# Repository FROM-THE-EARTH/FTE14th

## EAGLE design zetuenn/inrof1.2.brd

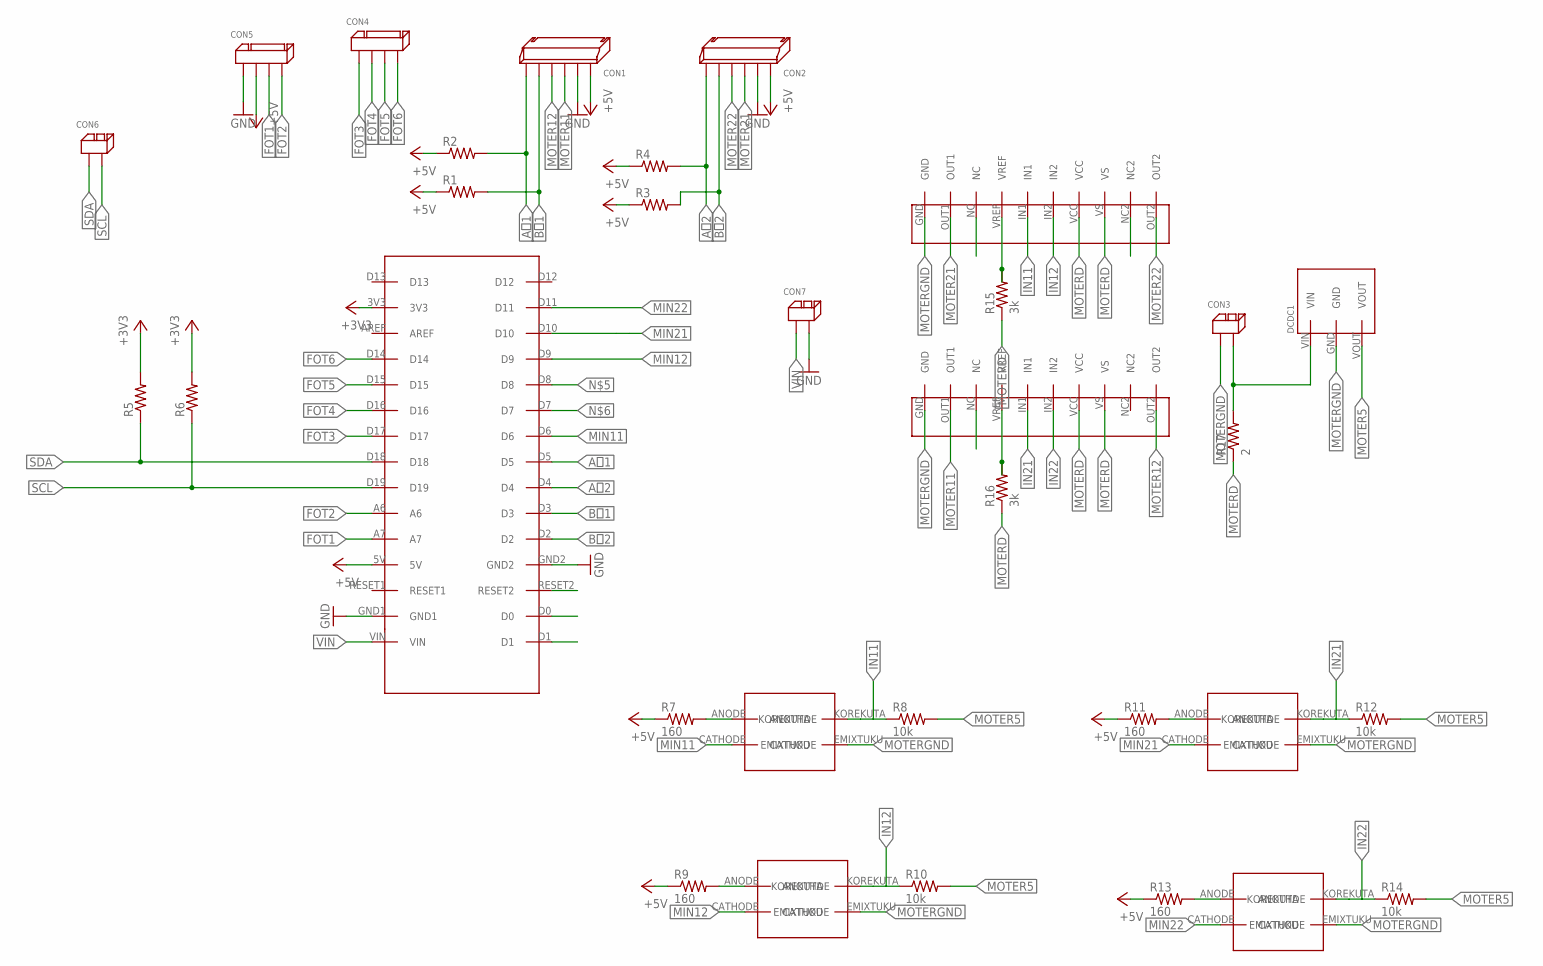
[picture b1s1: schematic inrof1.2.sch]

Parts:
CON1, CON2: 6PIN_SIDE
CON3, CON6, CON7: 2PIN
CON4, CON5: 4PIN
DCDC1: 5V1A_M78AR05-1
R1, R2, R3, R4, R5, R6: R-US_0204/7; 0204/7
R7, R9, R11, R13: 160; 0204/7
R8, R10, R12, R14: 10k; 0204/7
R15, R16: 3k; 0204/7
R17: 2; 0204/7
U$1: ARDUINONANO
U$2, U$3: TA7291P
U$4, U$5, U$6, U$7: TLP561

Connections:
+3V3: R5.2, R6.2, U$1.3V3
+5V: CON1.P$6, CON2.P$6, CON5.P$2, R1.1, R2.1, R3.1, R4.1, R7.1, R9.1, R11.1, R13.1, U$1.5V
A相1: CON1.P$1, R2.2, U$1.D5
A相2: CON2.P$1, R4.2, U$1.D4
B相1: CON1.P$2, R1.2, U$1.D3
B相2: CON2.P$2, R3.2, U$1.D2
FOT1: CON5.P$3, U$1.A7
FOT2: CON5.P$4, U$1.A6
FOT3: CON4.P$1, U$1.D17
FOT4: CON4.P$2, U$1.D16
FOT5: CON4.P$3, U$1.D15
FOT6: CON4.P$4, U$1.D14
GND: CON1.P$5, CON2.P$5, CON5.P$1, CON7.P$2, U$1.GND1, U$1.GND2
IN11: R8.1, U$2.IN1, U$4.KOREKUTA
IN12: R10.1, U$2.IN2, U$5.KOREKUTA
IN21: R12.1, U$3.IN1, U$6.KOREKUTA
IN22: R14.1, U$3.IN2, U$7.KOREKUTA
MIN11: U$1.D6, U$4.CATHODE
MIN12: U$1.D9, U$5.CATHODE
MIN21: U$1.D10, U$6.CATHODE
MIN22: U$1.D11, U$7.CATHODE
MOTER5: DCDC1.VOUT, R8.2, R10.2, R12.2, R14.2
MOTER11: CON1.P$4, U$3.OUT1
MOTER12: CON1.P$3, U$3.OUT2
MOTER21: CON2.P$4, U$2.OUT1
MOTER22: CON2.P$3, U$2.OUT2
MOTERD: CON3.P$2, DCDC1.VIN, R15.1, R16.1, R17.1, R17.2, U$2.VCC, U$2.VS, U$3.VCC, U$3.VS
MOTERGND: CON3.P$1, DCDC1.GND, U$2.GND, U$3.GND, U$4.EMIXTUKU, U$5.EMIXTUKU, U$6.EMIXTUKU, U$7.EMIXTUKU
unnamed: R7.2, U$4.ANODE (ANOTHDE)
unnamed: R15.2, U$2.VREF
unnamed: R16.2, U$3.VREF
unnamed: R9.2, U$5.ANODE (ANOTHDE)
unnamed: R11.2, U$6.ANODE (ANOTHDE)
unnamed: R13.2, U$7.ANODE (ANOTHDE)
SCL: CON6.P$2, R6.1, U$1.D19
SDA: CON6.P$1, R5.1, U$1.D18
VIN: CON7.P$1, U$1.VIN

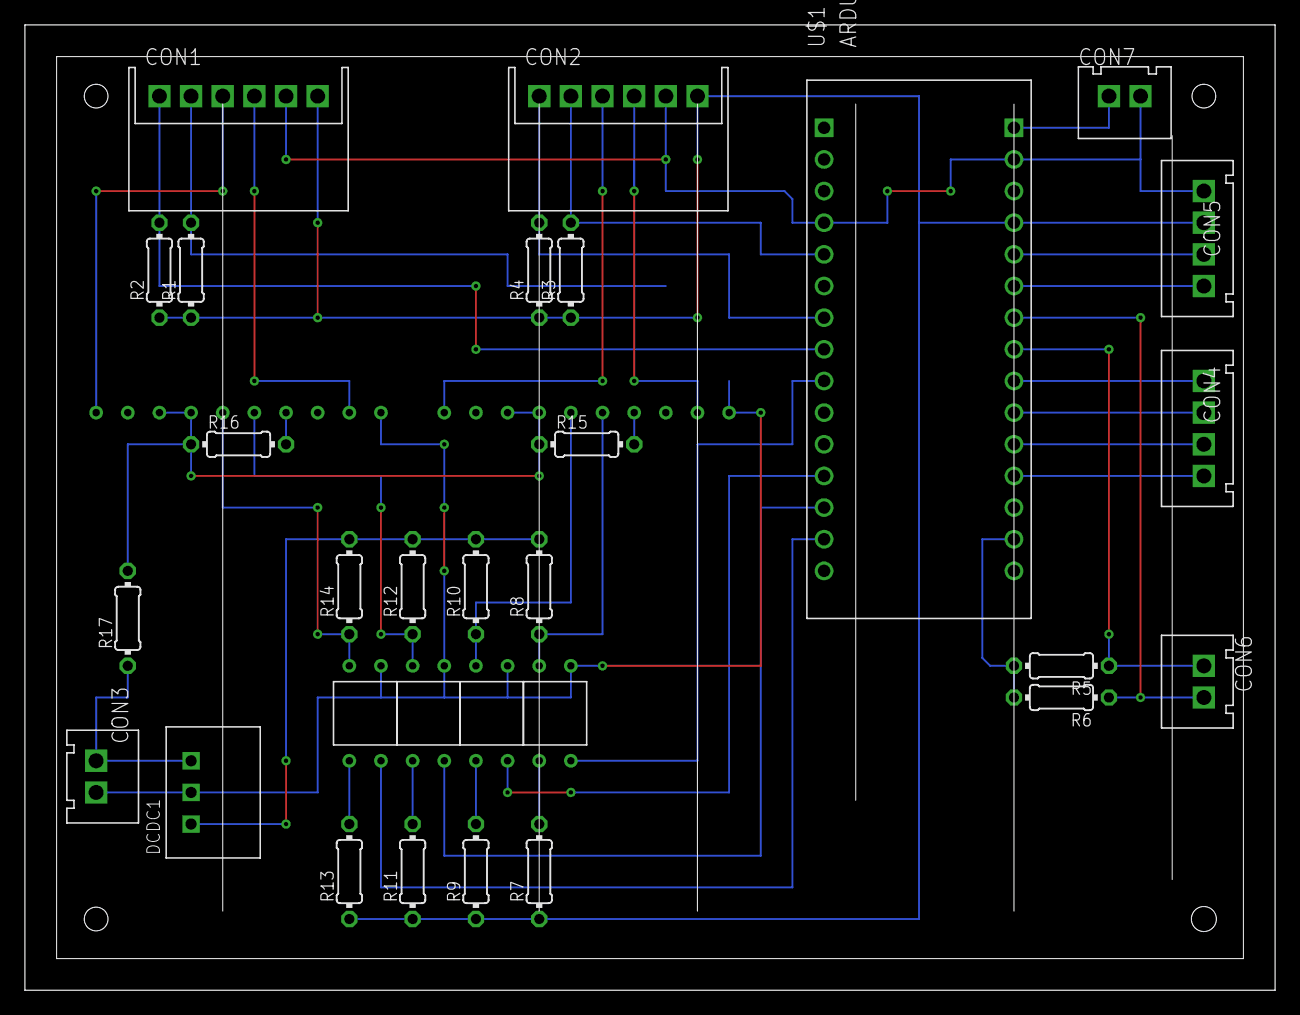
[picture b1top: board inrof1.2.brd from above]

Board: 2 copper layers, 100.3 x 77.5 mm, 32 parts (0 on the bottom side), 37 nets.

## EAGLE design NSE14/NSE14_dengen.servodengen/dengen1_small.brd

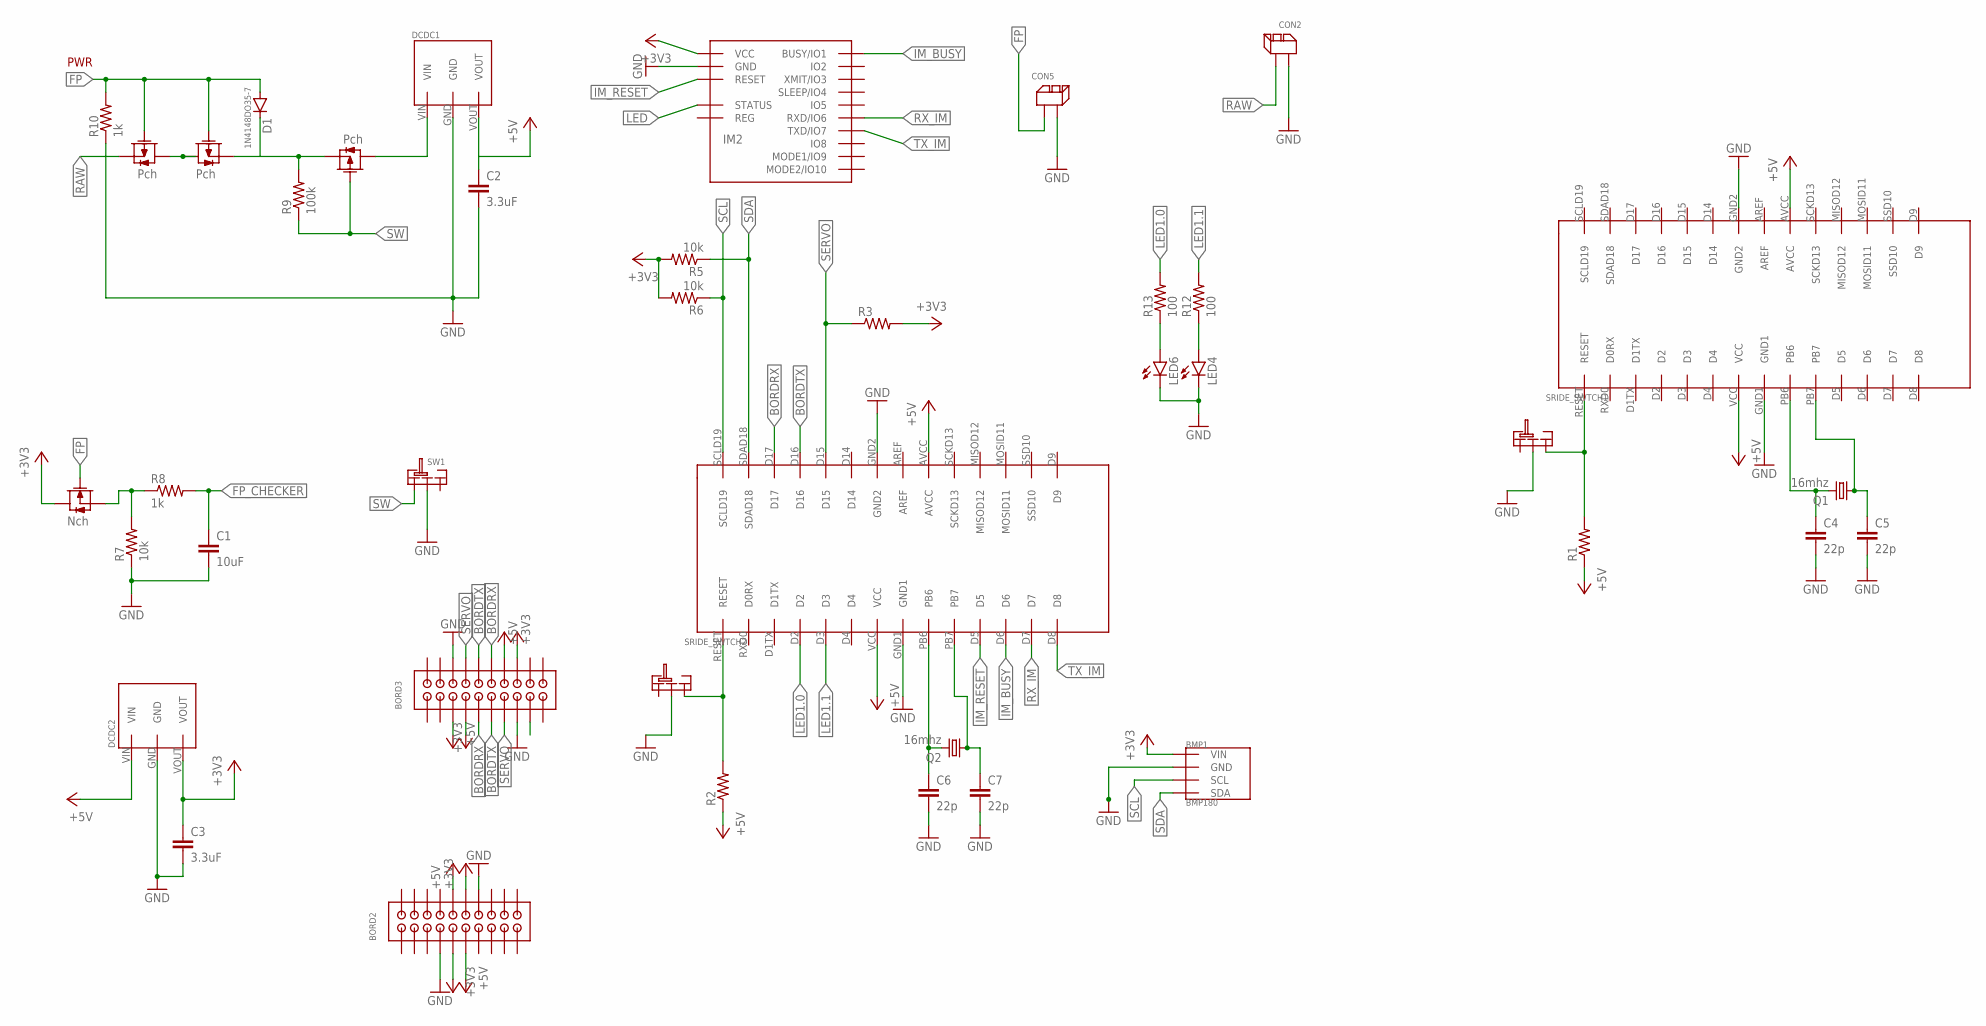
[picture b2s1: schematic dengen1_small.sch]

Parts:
BMP1: BMP180; GY-68
BORD2, BORD3: 2X10
C1: 10uF; C025-024X044
C2, C3: 3.3uF; C025-024X044
C4, C5, C6, C7: 22p; C025-024X044
CON2, CON5: 2PIN
D1: 1N4148DO35-7; DO35-7
DCDC1: 5V1A_M78AR05-1
DCDC2: 3.3V1A_M78AR033-1
IM2: IM920_IM920C
LED4, LED6: LED5MM
Q1, Q2: 16mhz; HC49/S
R1, R2, R3: R-US_0204/7; 0204/7
R5, R6, R7: 10k; 0204/7
R8, R10: 1k; 0204/7
R9: 100k; 0204/7
R12, R13: 100; 0204/7
SRIDE_SWTCH1, SRIDE_SWTCH2: SRIDE_SWITCH
SW1: SRIDE_SWITCH
U$1, U$6: ATMEGA238P; ATMEGA328P
U$2, U$4, U$5: 2SJ681-PCH; 2SJ681
U$3: 2SK4017-NCH; 2SK4017

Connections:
+3V3: BMP1.P1 (VIN), BORD2.P$9, BORD2.P$12, BORD3.P$5, BORD3.P$16, C3.1, DCDC2.VOUT, IM2.$P17 (VCC), R3.2, R5.2, R6.2, U$3.DRAIN
+5V: BORD2.P$10, BORD2.P$11, BORD3.P$7, BORD3.P$14, C2.1, DCDC1.VOUT, DCDC2.VIN, R1.1, R2.1, U$1.AVCC, U$1.VCC, U$6.AVCC, U$6.VCC
+5V1: DCDC1.VIN, U$5.DRAIN
BORDRX: BORD3.P$9, BORD3.P$12, U$6.D17
BORDTX: BORD3.P$10, BORD3.P$11, U$6.D16
FP: CON5.P$1, D1.A, R10.2, U$2.GATE, U$3.GATE, U$4.GATE
FP_CHECKER: C1.1, R8.2
GND: BMP1.P2 (GND), BORD2.P$7, BORD2.P$14, BORD3.P$6, BORD3.P$15, C1.2, C2.2, C3.2, C4.2, C5.2, C6.2, C7.2, CON2.P$1, CON5.P$2, DCDC1.GND, DCDC2.GND, IM2.$P18 (GND), LED4.K (C), LED6.K (C), R7.1, R10.1, SRIDE_SWTCH1.LR, SRIDE_SWTCH2.LR, SW1.LR, U$1.GND1, U$1.GND2, U$6.GND1, U$6.GND2
IM_BUSY: IM2.$P1 (BUSY/IO1), U$6.D6
IM_RESET: IM2.$P19 (RESET), U$6.D5
LED: IM2.$P15 (STATUS)
LED1.0: R13.2, U$6.D2
LED1.1: R12.2, U$6.D3
unnamed: U$2.DRAIN, U$4.DRAIN
unnamed: C6.1, Q2.2, U$6.PB6
unnamed: D1.C, R9.2, U$4.SOURCE, U$5.SOURCE
unnamed: C7.1, Q2.1, U$6.PB7
unnamed: C5.1, Q1.1, U$1.PB7
unnamed: R1.2, SRIDE_SWTCH1.R, U$1.RESET
unnamed: C4.1, Q1.2, U$1.PB6
unnamed: R2.2, SRIDE_SWTCH2.R, U$6.RESET
unnamed: LED6.A, R13.1
unnamed: LED4.A, R12.1
unnamed: R7.2, R8.1, U$3.SOURCE
RAW: CON2.P$2, U$2.SOURCE
RX_IM: IM2.$P6 (RXD/IO6), U$6.D7
SCL: BMP1.P3 (SCL), R6.1, U$6.SCLD19
SDA: BMP1.P4 (SDA), R5.1, U$6.SDAD18
SERVO: BORD3.P$8, BORD3.P$13, R3.1, U$6.D15
SW: R9.1, SW1.L, U$5.GATE
TX_IM: IM2.$P7 (TXD/IO7), U$6.D8

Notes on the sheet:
PWR

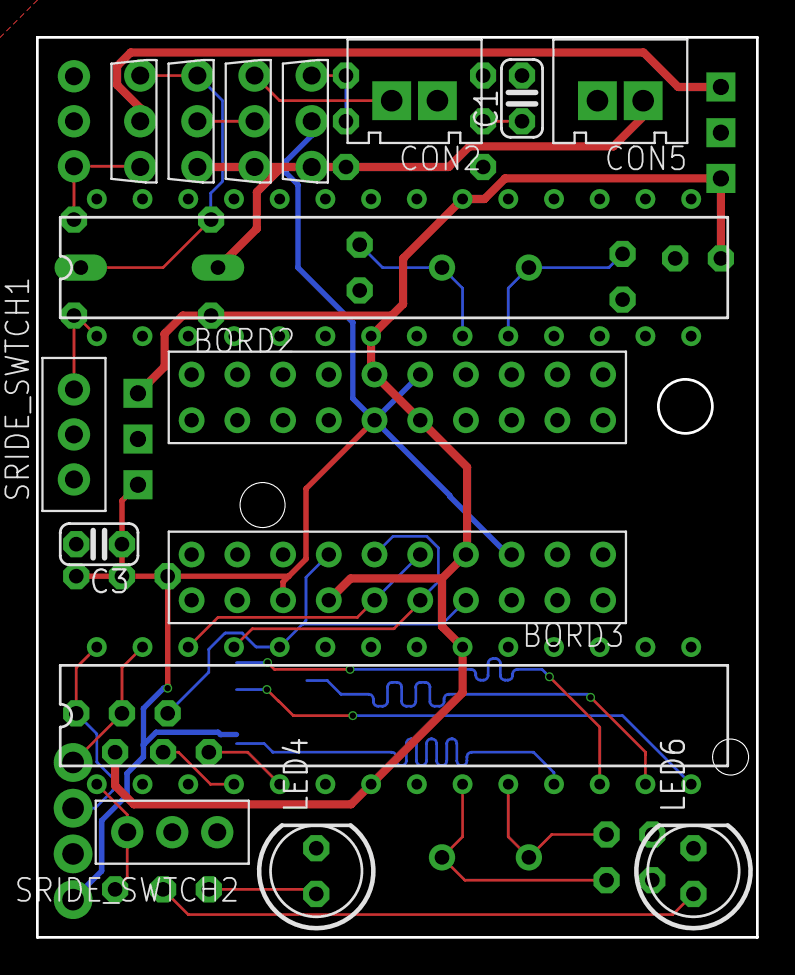
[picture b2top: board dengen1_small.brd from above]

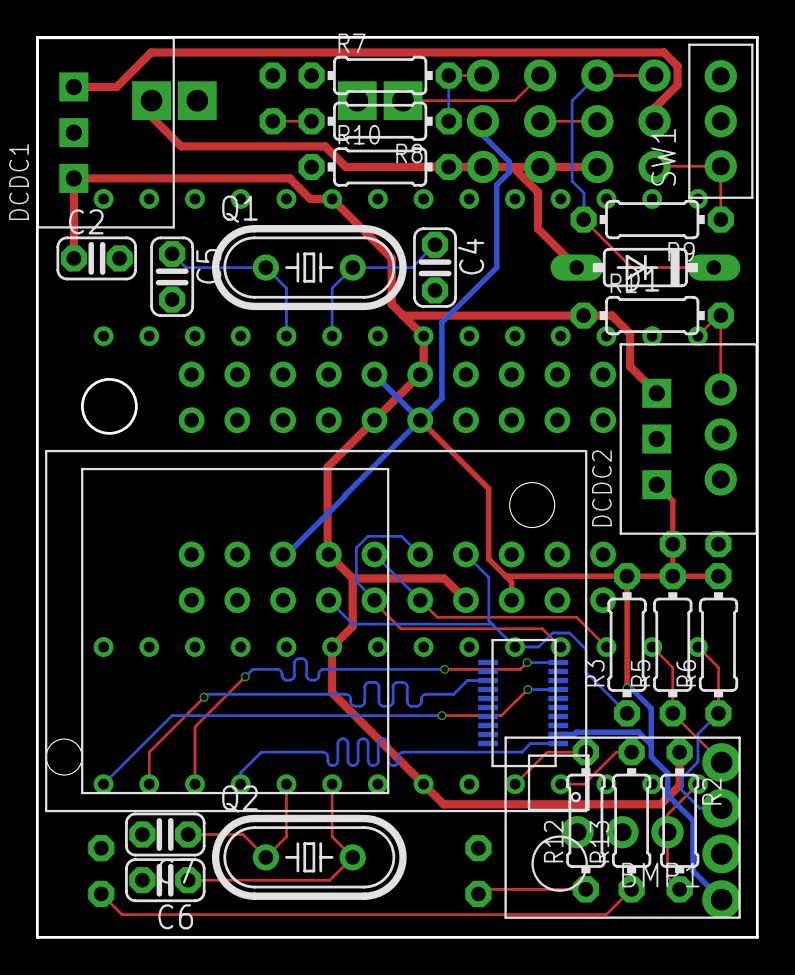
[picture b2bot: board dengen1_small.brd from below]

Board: 2 copper layers, 40.0 x 50.0 mm, 40 parts (24 on the bottom side), 30 nets.

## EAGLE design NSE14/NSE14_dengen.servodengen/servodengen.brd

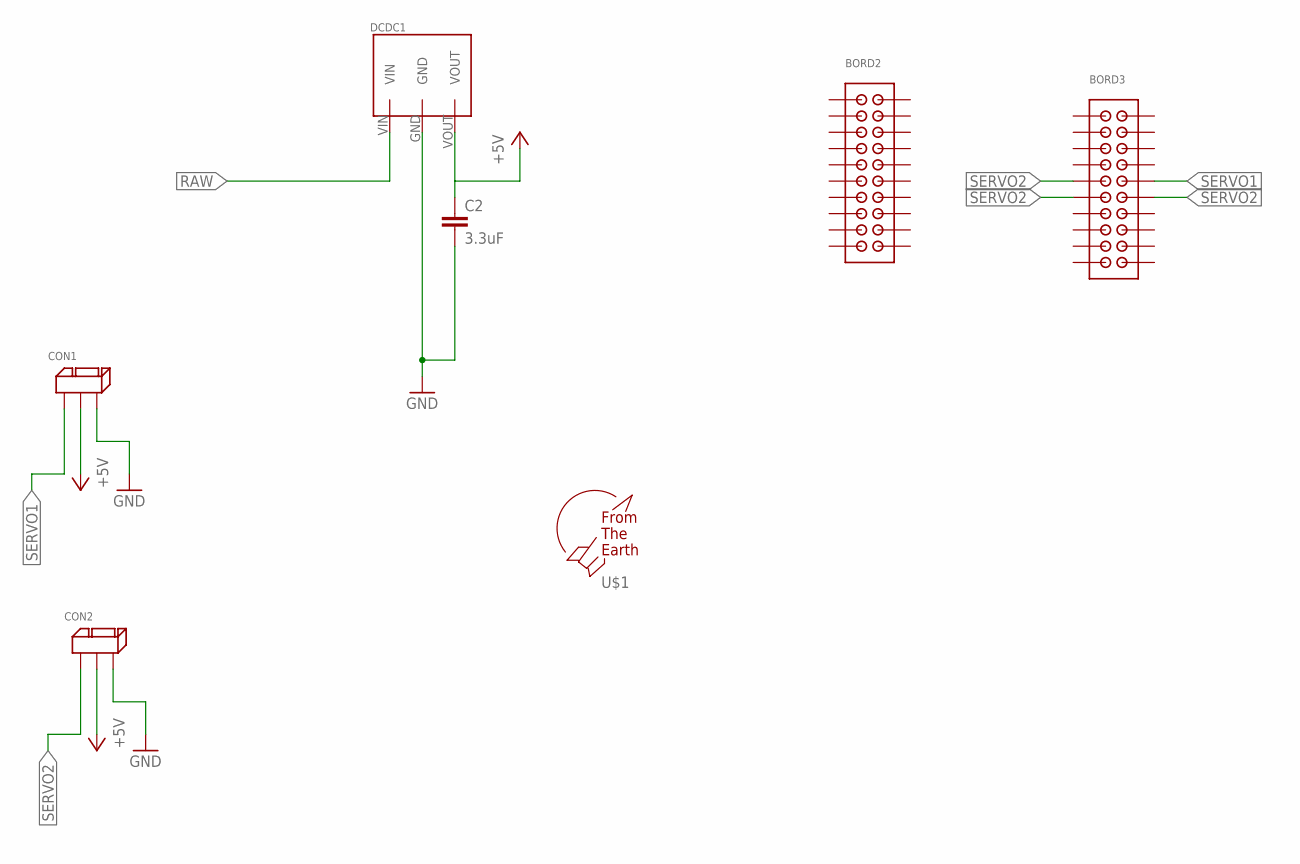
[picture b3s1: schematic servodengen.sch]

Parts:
BORD2, BORD3: 2X10
C2: 3.3uF; C025-024X044
CON1, CON2: 3PIN
DCDC1: 5V1A_M78AR05-1
U$1: F.T.E.LOGO; LOGO

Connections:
+5V: C2.1, CON1.P$2, CON2.P$2, DCDC1.VOUT
GND: C2.2, CON1.P$3, CON2.P$3, DCDC1.GND
RAW: DCDC1.VIN
SERVO1: BORD3.P$10, CON1.P$1
SERVO2: BORD3.P$9, BORD3.P$11, BORD3.P$12, CON2.P$1

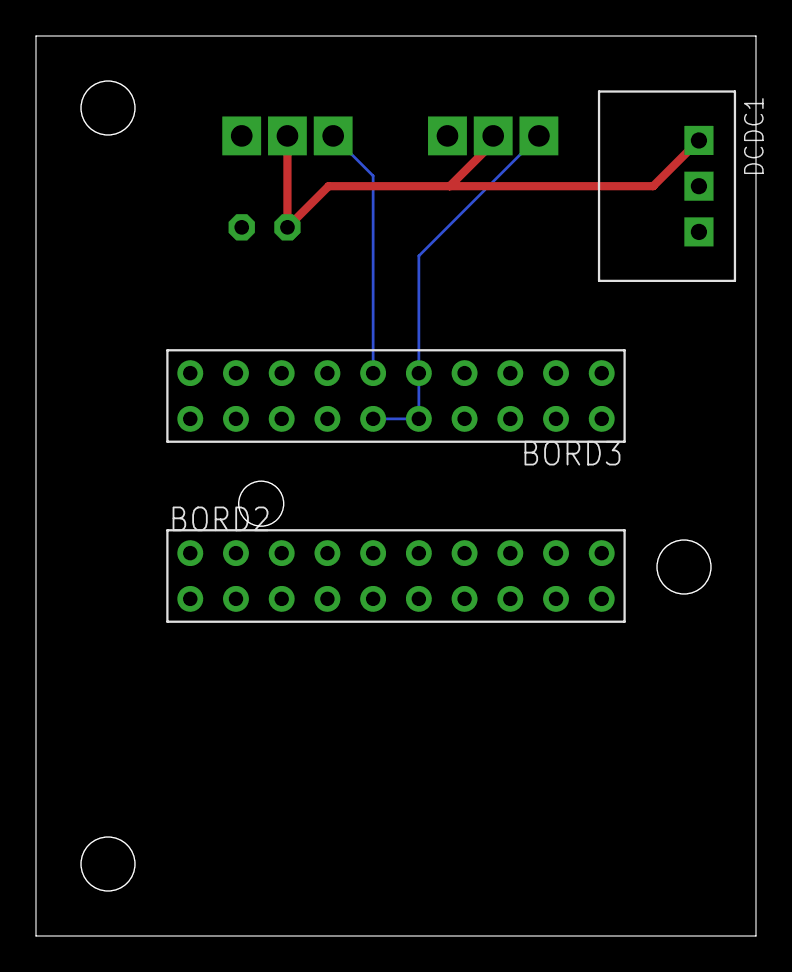
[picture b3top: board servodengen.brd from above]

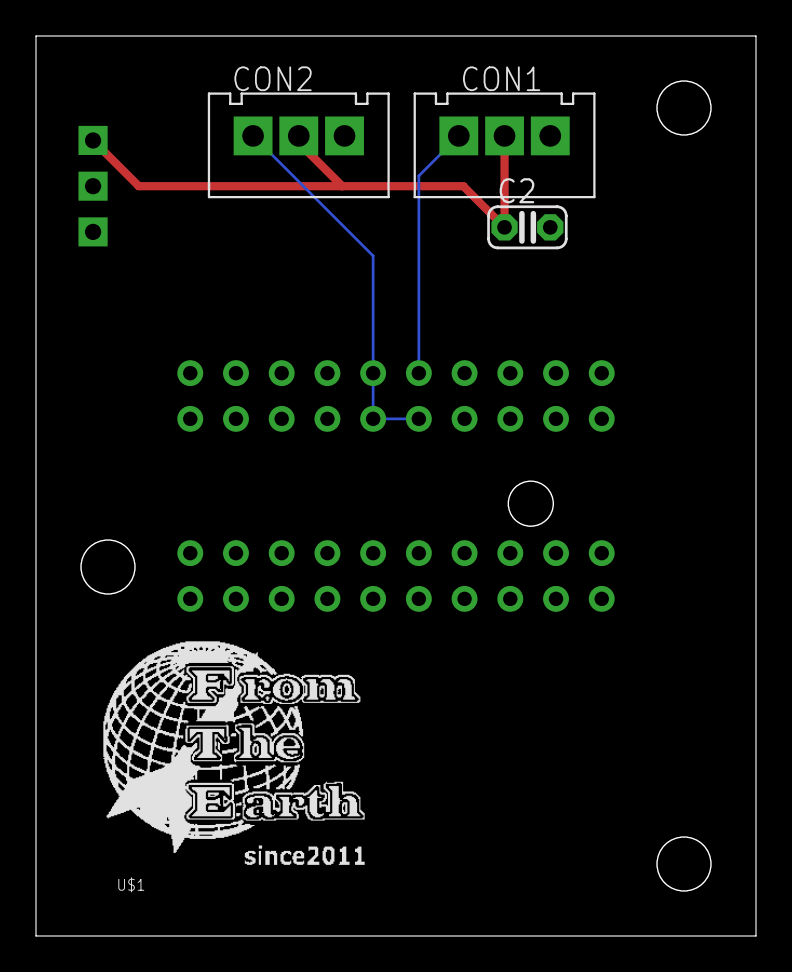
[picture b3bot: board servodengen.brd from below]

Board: 2 copper layers, 40.0 x 50.0 mm, 7 parts (4 on the bottom side), 4 nets.

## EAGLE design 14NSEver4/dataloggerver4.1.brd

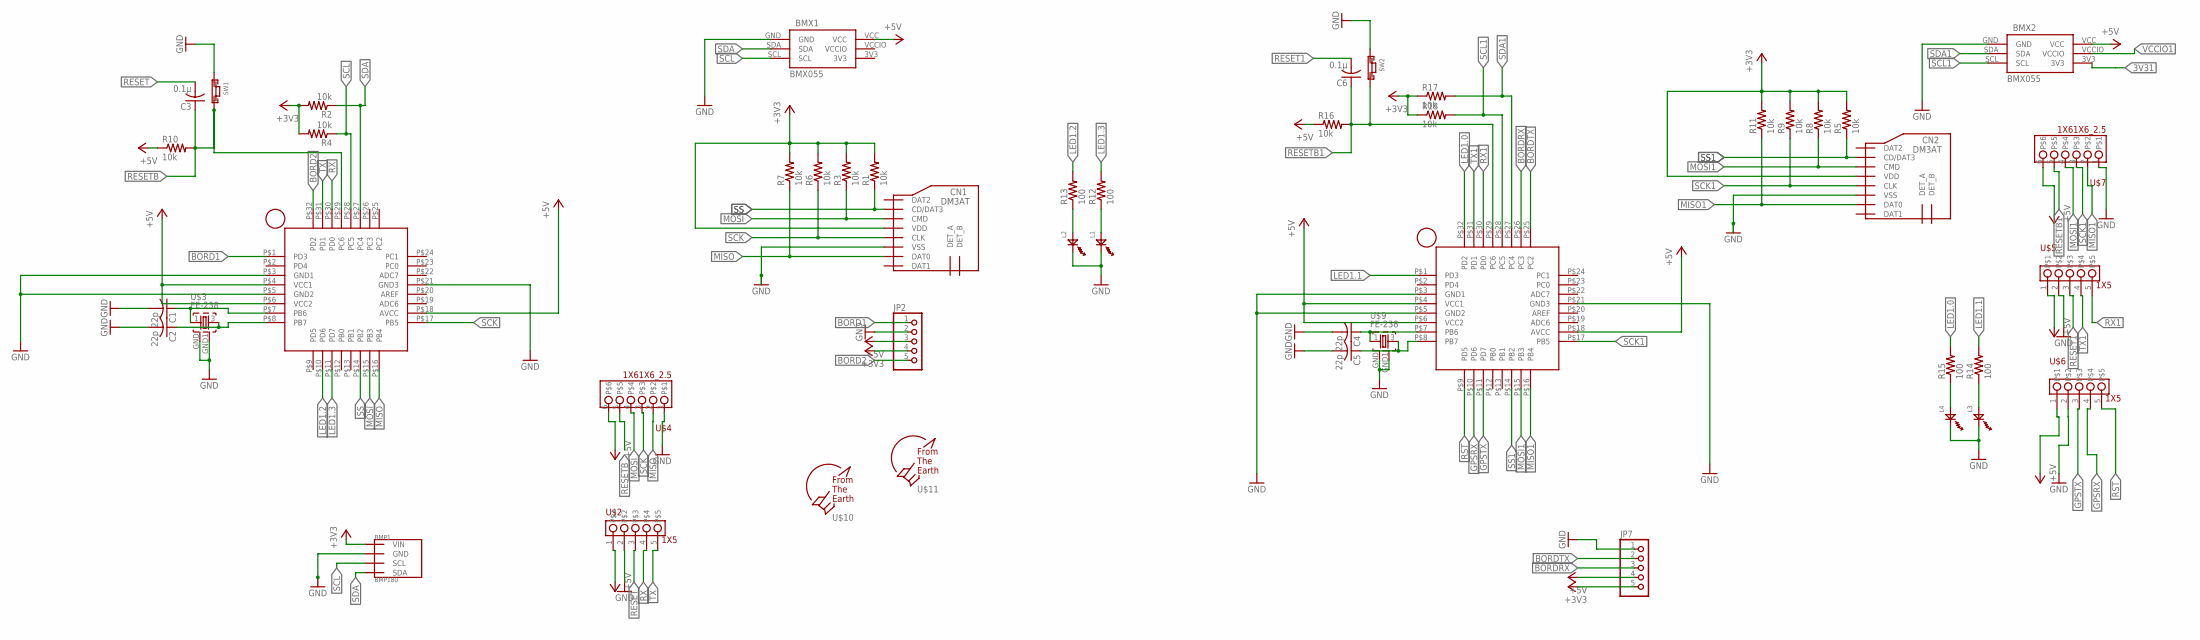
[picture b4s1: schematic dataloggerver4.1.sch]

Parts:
BMP1: BMP180; GY-68
BMX1, BMX2: BMX055
C1, C2, C4, C5: 22p; C1608
C3, C6: 0.1μ; C1608
CN1, CN2: DM3AT
JP2, JP7: PINHD-1X5; 1X05
L1, L2, L3, L4: OSXX1608C1A
R1, R2, R3, R4, R5, R6, R7, R8, R9, R10, R11, R16, R17, R18: 10k; R0603
R12, R13, R14, R15: 100; R0603
SW1, SW2: TVAF06-A020B-R
U$1, U$8: ATMEGA328P-AUATMEGA328P-AU; ATMEGA328P-AU
U$2, U$5, U$6: 1X5; HDRVR5W64P254_1X5_1310X250X865B
U$3, U$9: FE-238; OSCCC300X230X120N
U$4, U$7: 1X61X6_2.5; HDRVR6W64P254_1X6_1564X250X865B
U$10, U$11: F.T.E.LOGO; LOGO

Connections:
3V3: BMX1.3V3
3V31: BMX2.3V3
+3V3: BMP1.P1 (VIN), CN1.VDD, CN2.VDD, JP2.4, JP7.5, R1.2, R2.2, R3.2, R4.2, R5.2, R6.2, R7.2, R8.2, R9.2, R11.2, R17.1, R18.1
+5V: BMX1.VCC, BMX2.VCC, JP2.3, JP7.4, R10.1, R16.1, U$1.P$4 (VCC1), U$1.P$6 (VCC2), U$1.P$18 (AVCC), U$2.1, U$4.6, U$5.1, U$6.1, U$7.6, U$8.P$4 (VCC1), U$8.P$6 (VCC2), U$8.P$18 (AVCC)
BORD1: JP2.1, U$8.P$1 (PD3)
BORD2: JP2.5, U$8.P$32 (PD2)
BORDRX: JP7.3, U$1.P$26 (PC3)
BORDTX: JP7.2, U$1.P$25 (PC2)
GND: BMP1.P2 (GND), BMX1.GND, BMX2.GND, C1.2, C2.2, C4.2, C5.2, CN1.VSS, CN2.VSS, JP2.2, JP7.1, L1.CT, L2.CT, L3.CT, L4.CT, SW1.P$1, SW2.P$1, U$1.P$3 (GND1), U$1.P$5 (GND2), U$1.P$21 (GND3), U$2.2, U$3.GND, U$3.GND1, U$4.1, U$5.2, U$6.2, U$7.1, U$8.P$3 (GND1), U$8.P$5 (GND2), U$8.P$21 (GND3), U$9.GND, U$9.GND1
GPSRX: U$1.P$10 (PD6), U$6.4
GPSTX: U$1.P$11 (PD7), U$6.3
LED1.0: R15.2, U$1.P$32 (PD2)
LED1.1: R14.2, U$1.P$1 (PD3)
LED1.2: R13.2, U$8.P$10 (PD6)
LED1.3: R12.2, U$8.P$11 (PD7)
MISO: CN1.DAT0, R7.1, U$4.2, U$8.P$16 (PB4)
MISO1: CN2.DAT0, R11.1, U$1.P$16 (PB4), U$7.2
MOSI: CN1.CMD, R3.1, U$4.4, U$8.P$15 (PB3)
MOSI1: CN2.CMD, R8.1, U$1.P$15 (PB3), U$7.4
unnamed: L2.AN, R13.1
unnamed: L4.AN, R15.1
unnamed: C4.1, U$1.P$7 (PB6), U$9.1
unnamed: L1.AN, R12.1
unnamed: L3.AN, R14.1
unnamed: C5.1, U$1.P$8 (PB7), U$9.3
unnamed: C1.1, U$3.1, U$8.P$7 (PB6)
unnamed: C2.1, U$3.3, U$8.P$8 (PB7)
RESET: C3.2, U$2.3
RESET1: C6.2, U$5.3
RESETB: C3.1, R10.2, SW1.P$2, U$4.5, U$8.P$29 (PC6)
RESETB1: C6.1, R16.2, SW2.P$2, U$1.P$29 (PC6), U$7.5
RST: U$1.P$9 (PD5), U$6.5
RX: U$2.4, U$8.P$30 (PD0)
RX1: U$1.P$30 (PD0), U$5.5
SCK: CN1.CLK, R6.1, U$4.3, U$8.P$17 (PB5)
SCK1: CN2.CLK, R9.1, U$1.P$17 (PB5), U$7.3
SCL: BMP1.P3 (SCL), BMX1.SCL, R4.1, U$8.P$28 (PC5)
SCL1: BMX2.SCL, R18.2, U$1.P$28 (PC5)
SDA: BMP1.P4 (SDA), BMX1.SDA, R2.1, U$8.P$27 (PC4)
SDA1: BMX2.SDA, R17.2, U$1.P$27 (PC4)
SS: CN1.CD/DAT3, R1.1, U$8.P$14 (PB2)
SS1: CN2.CD/DAT3, R5.1, U$1.P$14 (PB2)
TX: U$2.5, U$8.P$31 (PD1)
TX1: U$1.P$31 (PD1), U$5.4
VCCIO: BMX1.VCCIO
VCCIO1: BMX2.VCCIO

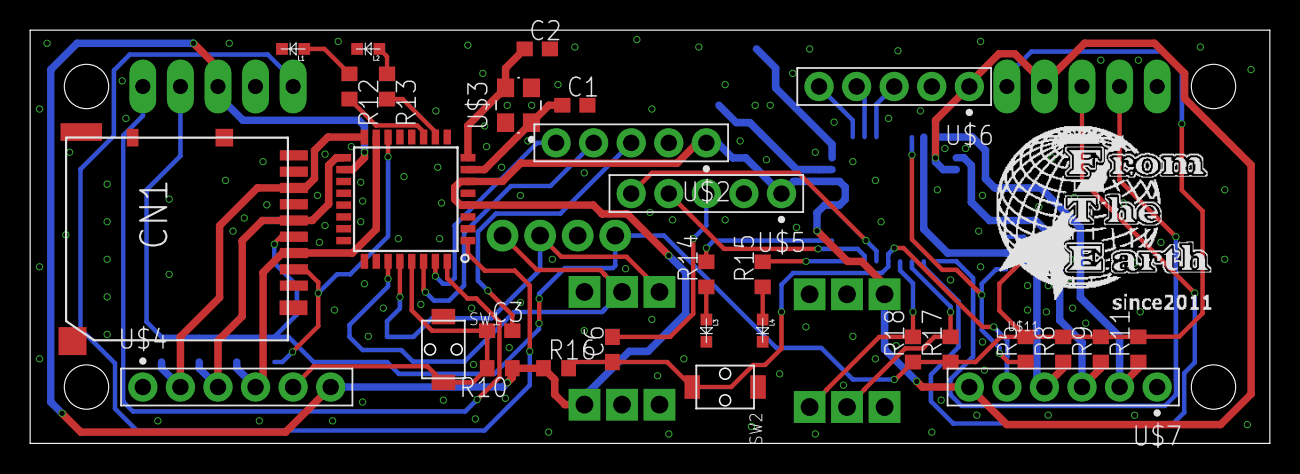
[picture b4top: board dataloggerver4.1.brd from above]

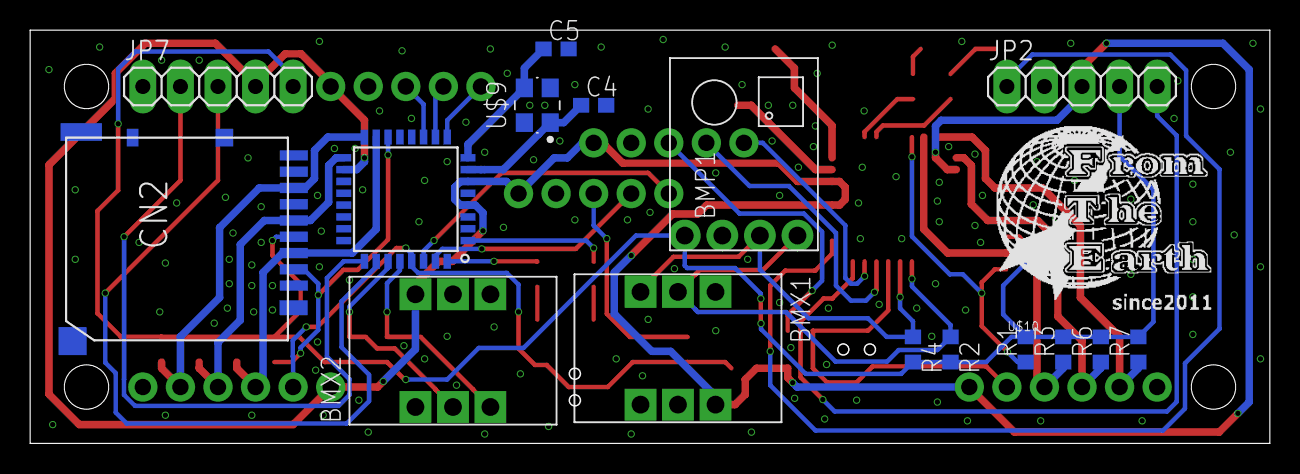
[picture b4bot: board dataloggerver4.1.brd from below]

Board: 2 copper layers, 83.8 x 27.9 mm, 48 parts (17 on the bottom side), 42 nets.

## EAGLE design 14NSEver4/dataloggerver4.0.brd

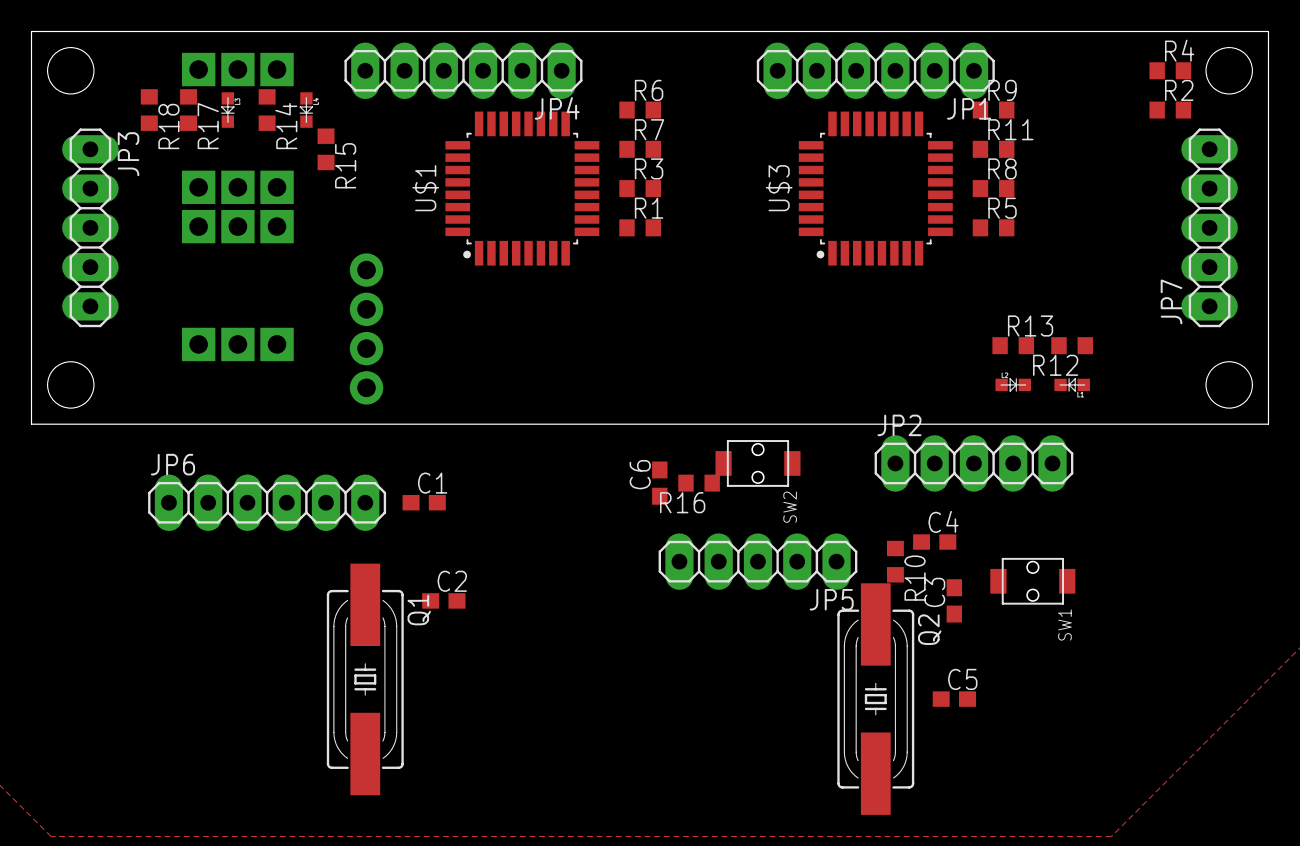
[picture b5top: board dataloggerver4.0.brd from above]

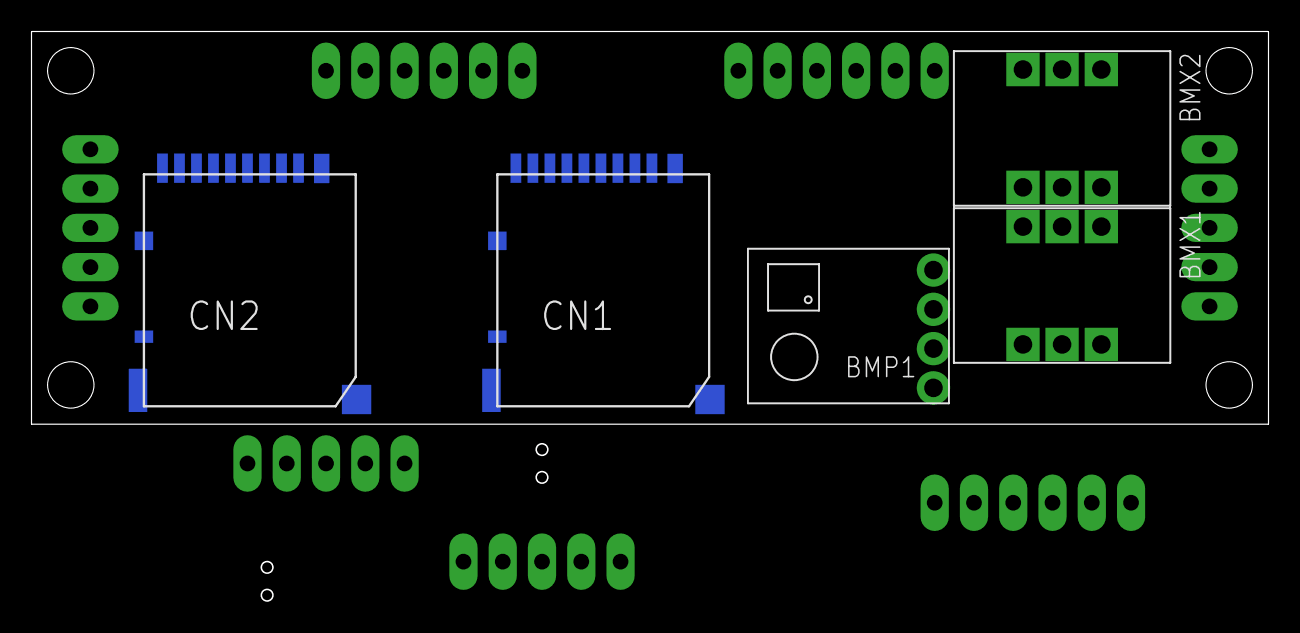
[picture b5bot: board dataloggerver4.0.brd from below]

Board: 2 copper layers, 80.0 x 36.8 mm, 46 parts (5 on the bottom side), 44 nets, no tracks yet.

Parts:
BMP1: BMP180; GY-68
BMX1, BMX2: BMX055
C1, C2, C4, C5: 22p; C1608
C3, C6: 0.1μ; C1608
CN1, CN2: DM3AT
JP1, JP4, JP6: 1X06
JP2, JP3, JP5, JP7: 1X05
L1, L2, L3, L4: OSXX1608C1A
Q1, Q2: 16mhz; HC49UP
R1, R2, R3, R4, R5, R6, R7, R8, R9, R10, R11, R16, R17, R18: 10k; R0603
R12, R13, R14, R15: 100; R0603
SW1, SW2: TVAF06-A020B-R
U$1, U$3: ATMEGA328P-AU; QFP80P900X900X120-32N

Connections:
3V3: BMX1.3V3, BMX2.3V3
+3V3: BMP1.P1, CN1.VDD, CN2.VDD, JP3.4, JP7.5, R1.2, R2.2, R3.2, R4.2, R5.2, R6.2, R7.2, R8.2, R9.2, R11.2, R17.1, R18.1
+5V: BMX1.VCC, BMX2.VCC, JP1.1, JP2.1, JP3.3, JP4.1, JP5.1, JP6.1, JP7.4, R10.1, R16.1, U$1.AVCC, U$1.VCC, U$1.VCC2, U$3.AVCC, U$3.VCC, U$3.VCC2
BORD1: JP3.1, U$1.PD3
BORD2: JP3.5, U$1.PD2
BORDRX: JP7.3, U$3.PC3
BORDTX: JP7.2, U$3.PC2
GND: BMP1.P2, BMX1.GND, BMX2.GND, C1.2, C2.2, C4.2, C5.2, CN1.VSS, CN2.VSS, JP1.2, JP2.2, JP3.2, JP4.2, JP5.2, JP6.2, JP7.1, L1.CT, L2.CT, L3.CT, L4.CT, SW1.P$1, SW2.P$1, U$1.GND, U$1.GND2, U$1.GND3, U$3.GND, U$3.GND2, U$3.GND3
GPSRX: JP6.4, U$3.PD6
GPSTX: JP6.3, U$3.PD7
LED1.0: R15.2, U$3.PD2
LED1.1: R14.2, U$3.PD3
LED1.2: R13.2, U$1.PD6
LED1.3: R12.2, U$1.PD7
MISO: CN1.DAT0, JP1.4, R7.1, U$1.PB4MISO
MISO1: CN2.DAT0, JP4.4, R11.1, U$3.PB4MISO
MOSI: CN1.CMD, JP1.5, R3.1, U$1.PB3MOSI
MOSI1: CN2.CMD, JP4.5, R8.1, U$3.PB3MOSI
unnamed: L2.AN, R13.1
unnamed: L4.AN, R15.1
unnamed: C4.1, Q2.1, U$3.PB6
unnamed: L1.AN, R12.1
unnamed: L3.AN, R14.1
unnamed: C1.1, Q1.1, U$1.PB6
unnamed: C2.1, Q1.2, U$1.PB7
unnamed: C5.1, Q2.2, U$3.PB7
RESET: C3.2, JP2.3
RESET1: C6.2, JP5.3
RESETB: C3.1, JP1.6, R10.2, SW1.P$2, U$1.PC6RESET
RESETB1: C6.1, JP4.6, R16.2, SW2.P$2, U$3.PC6RESET
RST: JP6.5, U$3.PD5
RX: JP2.4, U$1.PD0RX
RX1: JP5.4, U$3.PD0RX
SCK: CN1.CLK, JP1.3, R6.1, U$1.PB5
SCK1: CN2.CLK, JP4.3, R9.1, U$3.PB5
SCL: BMP1.P3, BMX1.SCL, R4.1, U$1.PC5SCL
SCL1: BMX2.SCL, R18.2, U$3.PC5SCL
SDA: BMP1.P4, BMX1.SDA, R2.1, U$1.PC4SDA
SDA1: BMX2.SDA, R17.2, U$3.PC4SDA
SS: CN1.CD/DAT3, R1.1, U$1.PB2SS
SS1: CN2.CD/DAT3, R5.1, U$3.PB2SS
TX: JP2.5, U$1.PD1TX
TX1: JP5.5, U$3.PD1TX
VCCIO: BMX1.VCCIO, BMX2.VCCIO

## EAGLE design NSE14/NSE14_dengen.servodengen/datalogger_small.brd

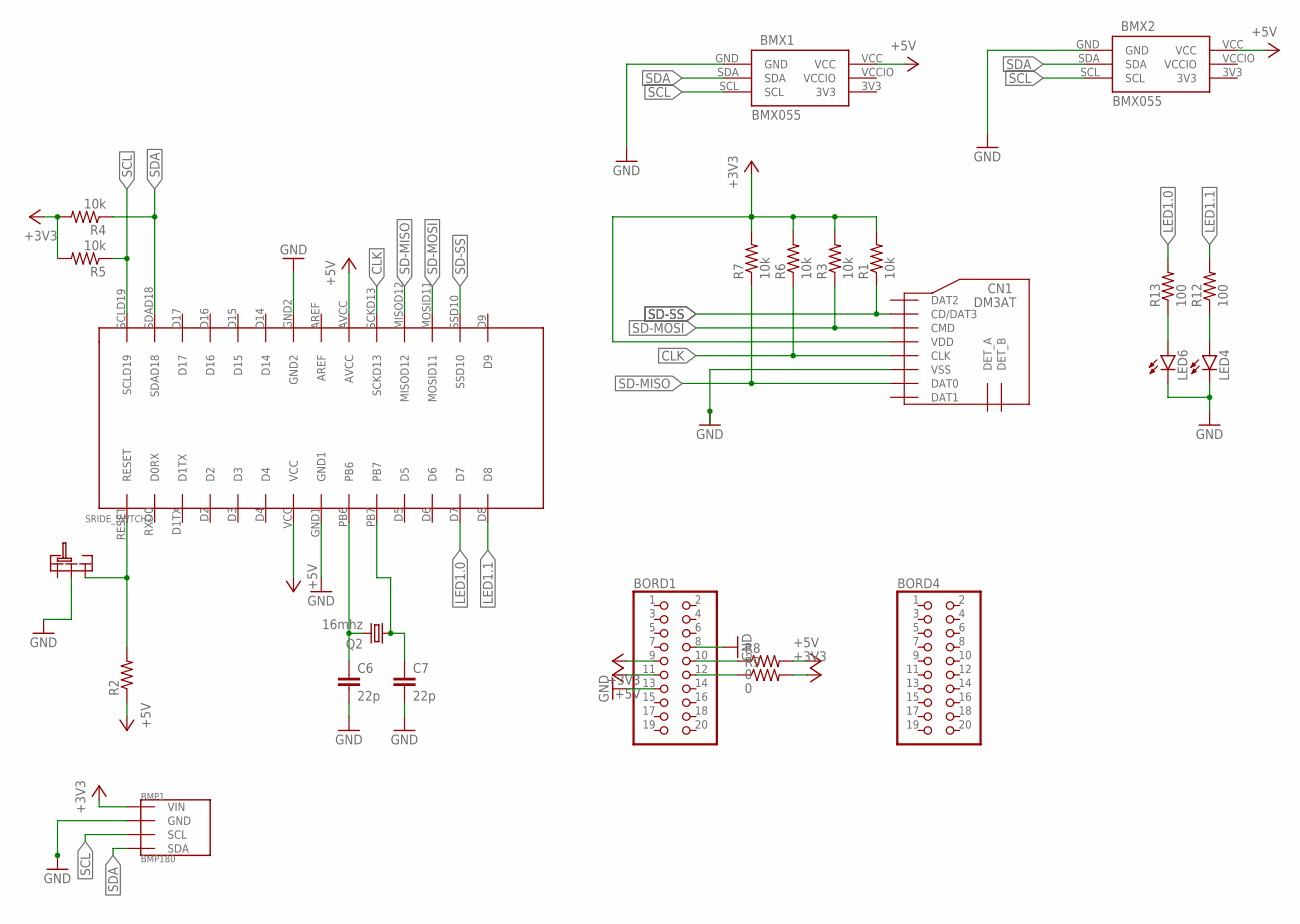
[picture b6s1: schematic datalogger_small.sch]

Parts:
BMP1: BMP180; GY-68
BMX1, BMX2: BMX055
BORD1, BORD4: PINHD-2X10/90; 2X10/90
C6, C7: 22p; C025-024X044
CN1: DM3AT
LED4, LED6: LED5MM
Q2: 16mhz; HC49/S
R1, R3, R4, R5, R6, R7: 10k; 0204/7
R2: R-US_0204/7; 0204/7
R8, R9: 0; 0204/7
R12, R13: 100; 0204/7
SRIDE_SWTCH2: SRIDE_SWITCH
U$6: ATMEGA238P; ATMEGA328P

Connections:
3V3: BMX1.3V3, BMX2.3V3
+3V3: BMP1.P1 (VIN), BORD1.9, CN1.VDD, R1.2, R3.2, R4.2, R5.2, R6.2, R7.2, R9.2
+5V: BMX1.VCC, BMX2.VCC, BORD1.11, R2.1, R8.2, U$6.AVCC, U$6.VCC
CLK: CN1.CLK, R6.1, U$6.SCKD13
GND: BMP1.P2 (GND), BMX1.GND, BMX2.GND, BORD1.8, BORD1.13, C6.2, C7.2, CN1.VSS, LED4.K (C), LED6.K (C), SRIDE_SWTCH2.LR, U$6.GND1, U$6.GND2
LED1.0: R13.2, U$6.D7
LED1.1: R12.2, U$6.D8
unnamed: LED6.A, R13.1
unnamed: C6.1, Q2.2, U$6.PB6
unnamed: C7.1, Q2.1, U$6.PB7
unnamed: BORD1.10, R8.1
unnamed: LED4.A, R12.1
unnamed: R2.2, SRIDE_SWTCH2.R, U$6.RESET
unnamed: BORD1.12, R9.1
SCL: BMP1.P3 (SCL), BMX1.SCL, BMX2.SCL, R5.1, U$6.SCLD19
SD-MISO: CN1.DAT0, R7.1, U$6.MISOD12
SD-MOSI: CN1.CMD, R3.1, U$6.MOSID11
SD-SS: CN1.CD/DAT3, R1.1, U$6.SSD10
SDA: BMP1.P4 (SDA), BMX1.SDA, BMX2.SDA, R4.1, U$6.SDAD18
VCCIO: BMX1.VCCIO, BMX2.VCCIO

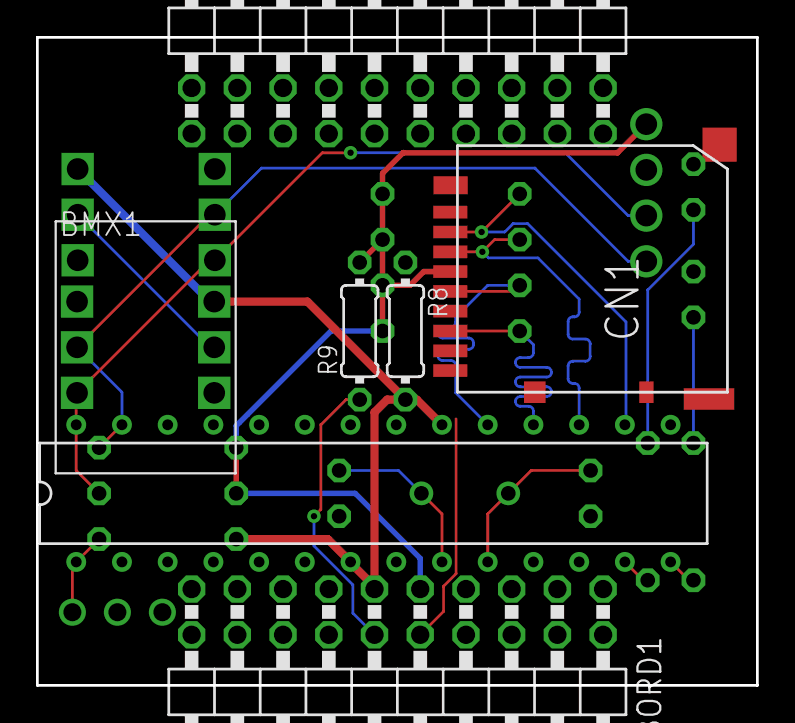
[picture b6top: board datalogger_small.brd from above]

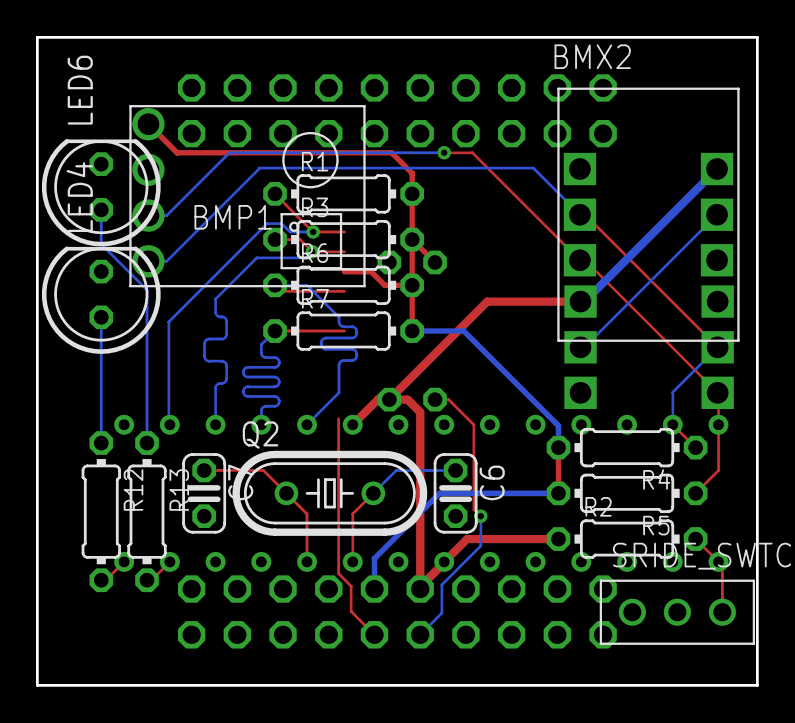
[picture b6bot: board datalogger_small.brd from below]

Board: 2 copper layers, 40.0 x 36.0 mm, 24 parts (17 on the bottom side), 20 nets.
